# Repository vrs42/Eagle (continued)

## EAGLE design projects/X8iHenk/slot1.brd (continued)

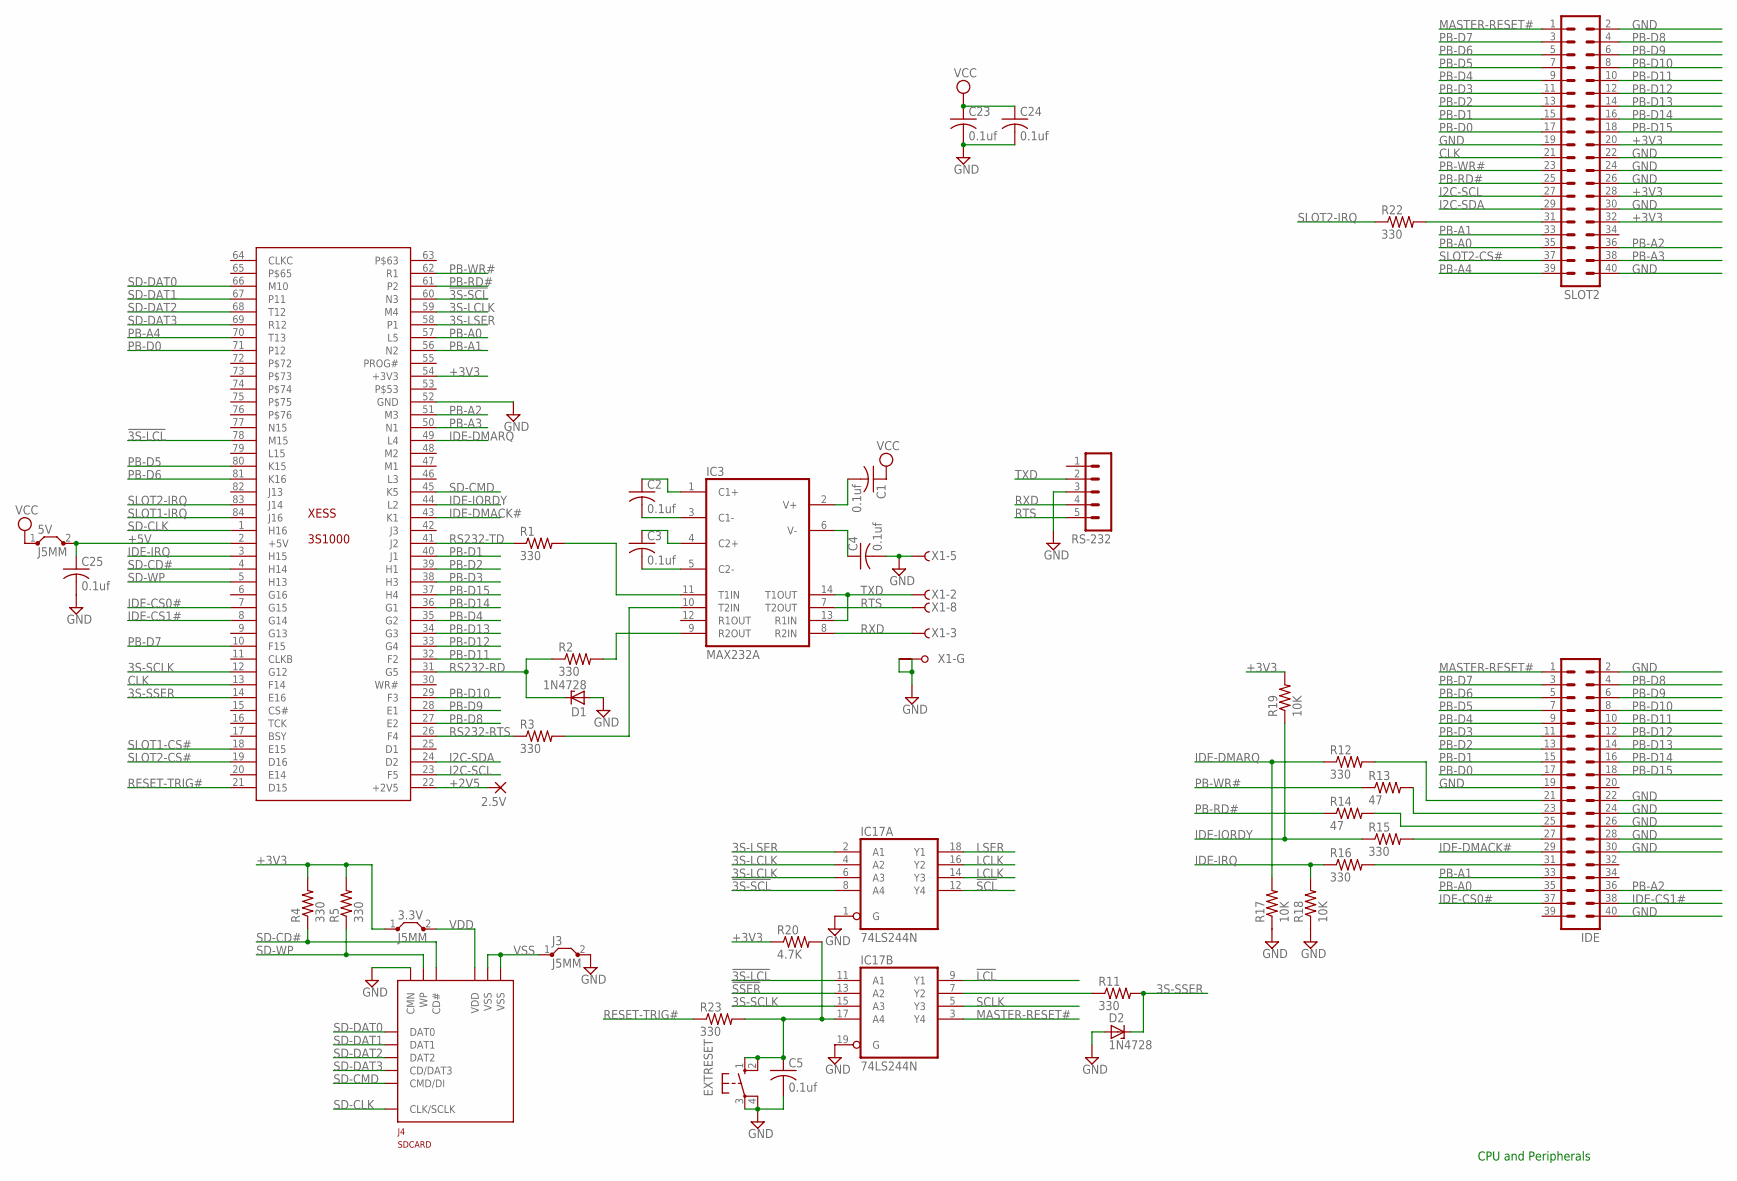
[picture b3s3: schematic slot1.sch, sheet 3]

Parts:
2.5V: 1,6/0,8
3.3V, 5V: J5MM; 05
C1, C2, C3, C4, C5, C23, C24, C25: 0.1uf; C050-025X075
D1, D2: 1N4728; DO41Z10
EXTRESET: 40-XX; B3F-40XX
IC3: MAX232A; DIL16
IC17: 74LS244N; DIL20
IDE: MA20-2
J3: J5MM; 05
J4: SDCARD; SCDA5A
R1, R2, R3, R4, R5, R11, R12, R15, R16, R22, R23: 330; 0207/10
R13, R14: 47; 0207/10
R17, R18, R19: 10K; 0207/10
R20: 4.7K; 0207/10
RS-232: MA05-1
SLOT2: MA20-2
X1: F09HPS; F09HP
XESS: 3S1000

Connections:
3S-LCLK: IC17.4 (A2), IC17.6 (A3), XESS.59 (M4)
3S-LSER: IC17.2 (A1), XESS.58 (P1)
3S-SCLK: IC17.15 (A3), XESS.12 (G12)
3S-SSER: D2.C, R11.2, XESS.14 (E16)
!3S-LCL: IC17.11 (A1), XESS.78 (M15)
!3S-SCL: IC17.8 (A4), XESS.60 (N3)
!LCL: IC17.9 (Y1)
!SCL: IC17.12 (Y4); also elsewhere on the board
!SSER: IC17.13 (A2); also elsewhere on the board
+2V5: 2.5V.1, XESS.22 (+2V5)
+3V3: 3.3V.1, R4.2, R5.2, R19.2, R20.1, SLOT2.20, SLOT2.28, SLOT2.32, XESS.54 (+3V3)
+5V: 5V.2, C25.1, XESS.2 (+5V)
CLK: SLOT2.21, XESS.13 (F14)
GND: C4.2, C5.2, C23.2, C24.2, C25.2, D1.A, D2.A, EXTRESET.3, EXTRESET.4 (P1), IC3.15 (GND), IC17.1 (G), IC17.10 (GND), IC17.19 (G), IDE.2, IDE.19, IDE.22, IDE.24, IDE.26, IDE.28, IDE.30, IDE.40, J3.2, J4.11 (CMN), J4.13 (GND), J4.14 (GND), R17.1, R18.1, RS-232.3, SLOT2.2, SLOT2.19, SLOT2.22, SLOT2.24, SLOT2.26, SLOT2.30, SLOT2.40, X1.5 (F), X1.G1, X1.G2, XESS.52 (GND); also elsewhere on the board
I2C-SCL: SLOT2.27, XESS.23 (F5)
I2C-SDA: SLOT2.29, XESS.24 (D2)
IDE-CS0#: IDE.37, XESS.7 (G15)
IDE-CS1#: IDE.38, XESS.8 (G14)
IDE-DMACK#: IDE.29, XESS.43 (K1)
IDE-DMARQ: R12.1, R17.2, XESS.49 (L4)
IDE-IORDY: R15.1, R19.1, XESS.44 (L2)
IDE-IRQ: R16.1, R18.2, XESS.3 (H15)
LCLK: IC17.14 (Y3), IC17.16 (Y2)
LSER: IC17.18 (Y1)
MASTER-RESET#: IC17.3 (Y4), IDE.1, SLOT2.1
unnamed: IC3.10 (T2IN), R3.2
unnamed: IC3.11 (T1IN), R1.2
unnamed: IC3.9 (R2OUT), R2.2
unnamed: C1.2, IC3.2 (V+)
unnamed: C2.2, IC3.3 (C1-)
unnamed: C2.1, IC3.1 (C1+)
unnamed: C4.1, IC3.6 (V-)
unnamed: C3.1, IC3.4 (C2+)
unnamed: C3.2, IC3.5 (C2-)
unnamed: IC17.7 (Y2), R11.1
unnamed: R22.2, SLOT2.31
unnamed: C5.1, EXTRESET.1 (S), EXTRESET.2 (S1), IC17.17 (A4), R20.2, R23.2
unnamed: IDE.31, R16.2
unnamed: IDE.27, R15.2
unnamed: IDE.25, R14.2
unnamed: IDE.23, R13.2
unnamed: IDE.21, R12.2
PB-A0: IDE.35, SLOT2.35, XESS.57 (L5); also elsewhere on the board
PB-A1: IDE.33, SLOT2.33, XESS.56 (N2)
PB-A2: IDE.36, SLOT2.36, XESS.51 (M3); also elsewhere on the board
PB-A3: SLOT2.38, XESS.50 (N1)
PB-A4: SLOT2.39, XESS.70 (T13)
PB-D0: IDE.17, SLOT2.17, XESS.71 (P12); also elsewhere on the board
PB-D1: IDE.15, SLOT2.15, XESS.40 (J1); also elsewhere on the board
PB-D2: IDE.13, SLOT2.13, XESS.39 (H1); also elsewhere on the board
PB-D3: IDE.11, SLOT2.11, XESS.38 (H3); also elsewhere on the board
PB-D4: IDE.9, SLOT2.9, XESS.35 (G2); also elsewhere on the board
PB-D5: IDE.7, SLOT2.7, XESS.80 (K15); also elsewhere on the board
PB-D6: IDE.5, SLOT2.5, XESS.81 (K16); also elsewhere on the board
PB-D7: IDE.3, SLOT2.3, XESS.10 (F15); also elsewhere on the board
PB-D8: IDE.4, SLOT2.4, XESS.27 (E2); also elsewhere on the board
PB-D9: IDE.6, SLOT2.6, XESS.28 (E1); also elsewhere on the board
PB-D10: IDE.8, SLOT2.8, XESS.29 (F3); also elsewhere on the board
PB-D11: IDE.10, SLOT2.10, XESS.32 (F2); also elsewhere on the board
PB-D12: IDE.12, SLOT2.12, XESS.33 (G4); also elsewhere on the board
PB-D13: IDE.14, SLOT2.14, XESS.34 (G3); also elsewhere on the board
PB-D14: IDE.16, SLOT2.16, XESS.36 (G1); also elsewhere on the board
PB-D15: IDE.18, SLOT2.18, XESS.37 (H4); also elsewhere on the board
PB-RD#: R14.1, SLOT2.25, XESS.61 (P2)
PB-WR#: R13.1, SLOT2.23, XESS.62 (R1); also elsewhere on the board
RESET-TRIG#: R23.1, XESS.21 (D15)
RS232-RD: D1.C, R2.1, XESS.31 (G5)
RS232-RTS: R3.1, XESS.26 (F4)
RS232-TD: R1.1, XESS.41 (J2)
RTS: IC3.7 (T2OUT), RS-232.5, X1.8 (F)
RXD: IC3.8 (R2IN), RS-232.4, X1.3 (F)
SCLK: IC17.5 (Y3); also elsewhere on the board
SD-CD#: J4.10 (CD#), R4.1, XESS.4 (H14)
SD-CLK: J4.5 (CLK/SCLK), XESS.1 (H16)
SD-CMD: J4.2 (CMD/DI), XESS.45 (K5)
SD-DAT0: J4.7 (DAT0), XESS.66 (M10)
SD-DAT1: J4.8 (DAT1), XESS.67 (P11)
SD-DAT2: J4.9 (DAT2), XESS.68 (T12)
SD-DAT3: J4.1 (CD/DAT3), XESS.69 (R12)
SD-WP: J4.12 (WP), R5.1, XESS.5 (H13)
SLOT1-CS#: XESS.18 (E15); also elsewhere on the board
SLOT1-IRQ: XESS.84 (J16)
SLOT2-CS#: SLOT2.37, XESS.19 (D16)
SLOT2-IRQ: R22.1, XESS.83 (J14)
TXD: IC3.13 (R1IN), IC3.14 (T1OUT), RS-232.2, X1.2 (F)
VCC: 5V.1, C1.1, C23.1, C24.1, IC3.16 (VCC), IC17.20 (VCC); also elsewhere on the board
VDD: 3.3V.2, J4.4 (VDD)
VSS: J3.1, J4.3 (VSS), J4.6 (VSS)

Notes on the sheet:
CPU and Peripherals

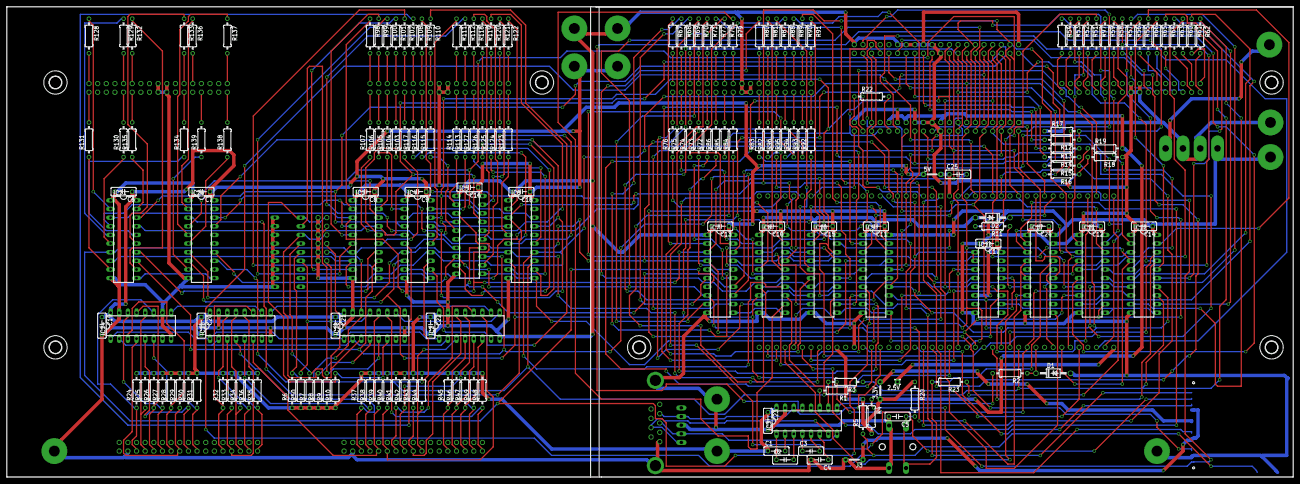
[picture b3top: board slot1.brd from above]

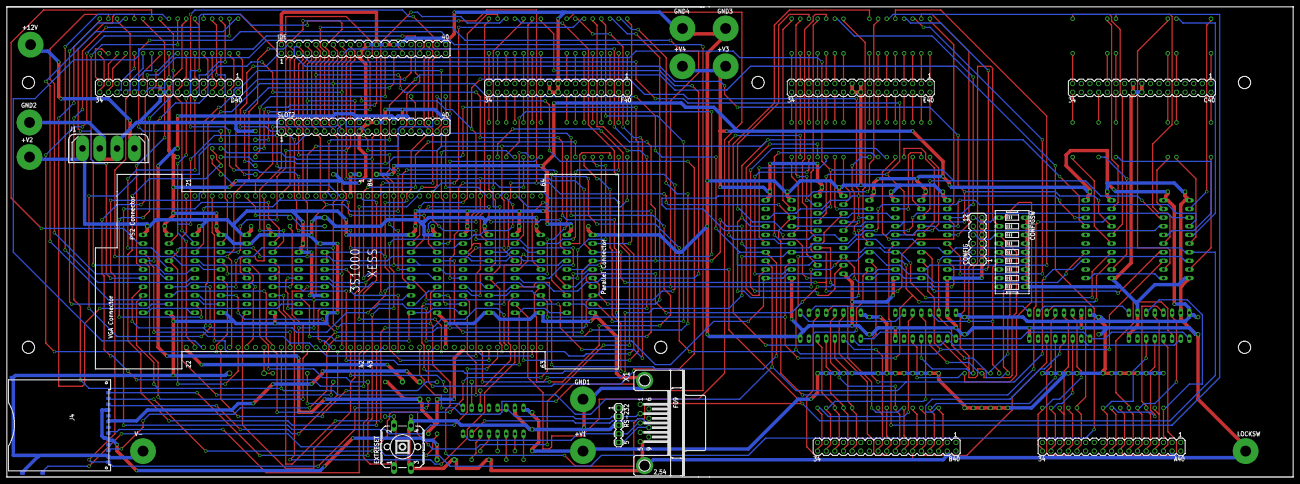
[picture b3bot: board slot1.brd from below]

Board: 2 copper layers, 377.8 x 138.1 mm, 221 parts (27 on the bottom side), 305 nets.

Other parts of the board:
U$5, U$6, U$7, U$8, U$9, U$11: 3,6

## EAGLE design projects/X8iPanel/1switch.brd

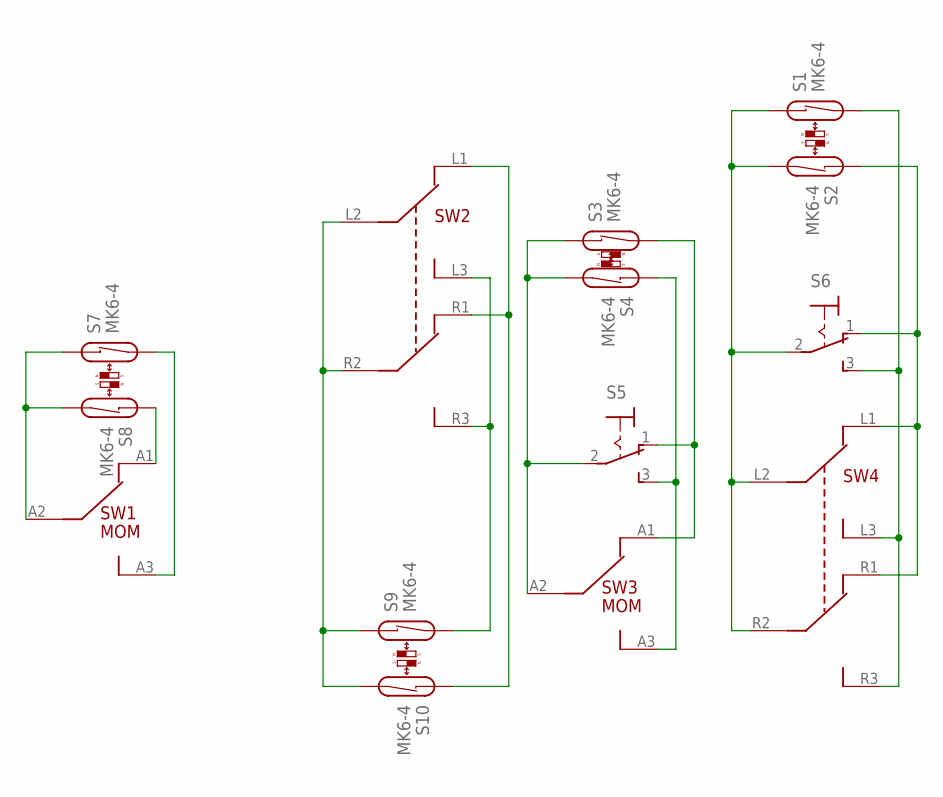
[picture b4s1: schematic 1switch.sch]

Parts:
S1, S2, S3, S4, S7, S8, S9, S10: MK6-4
S5, S6: M9040P7101V2; 7101MD9V21
SW1, SW3: SPDT8I
SW2, SW4: DPDT8I

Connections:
unnamed: S8.1, SW1.A1
unnamed: S7.2, SW1.A3
unnamed: S7.1, S8.2, SW1.A2
unnamed: S9.1, S10.2, SW2.L2 (A2), SW2.R2 (B2)
unnamed: S3.1, S4.2, S5.2, SW3.A2
unnamed: S9.2, SW2.L3 (A3), SW2.R3 (B3)
unnamed: S10.1, SW2.L1 (A1), SW2.R1 (B1)
unnamed: S4.1, S5.3 (S), SW3.A3
unnamed: S3.2, S5.1 (O), SW3.A1
unnamed: S1.1, S2.2, S6.2, SW4.L2 (A2), SW4.R2 (B2)
unnamed: S1.2, S6.3 (S), SW4.L3 (A3), SW4.R3 (B3)
unnamed: S2.1, S6.1 (O), SW4.L1 (A1), SW4.R1 (B1)

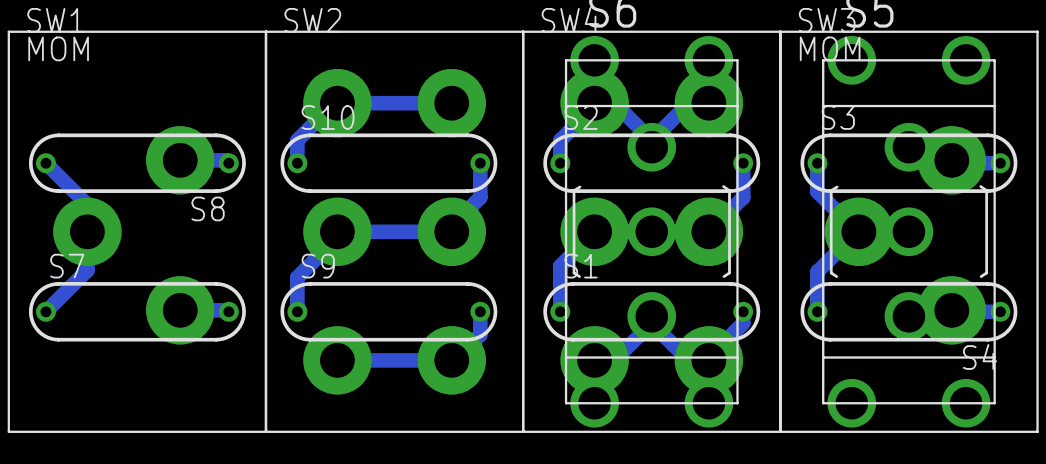
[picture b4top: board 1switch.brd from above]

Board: 2 copper layers, 14 parts (0 on the bottom side), 12 nets.

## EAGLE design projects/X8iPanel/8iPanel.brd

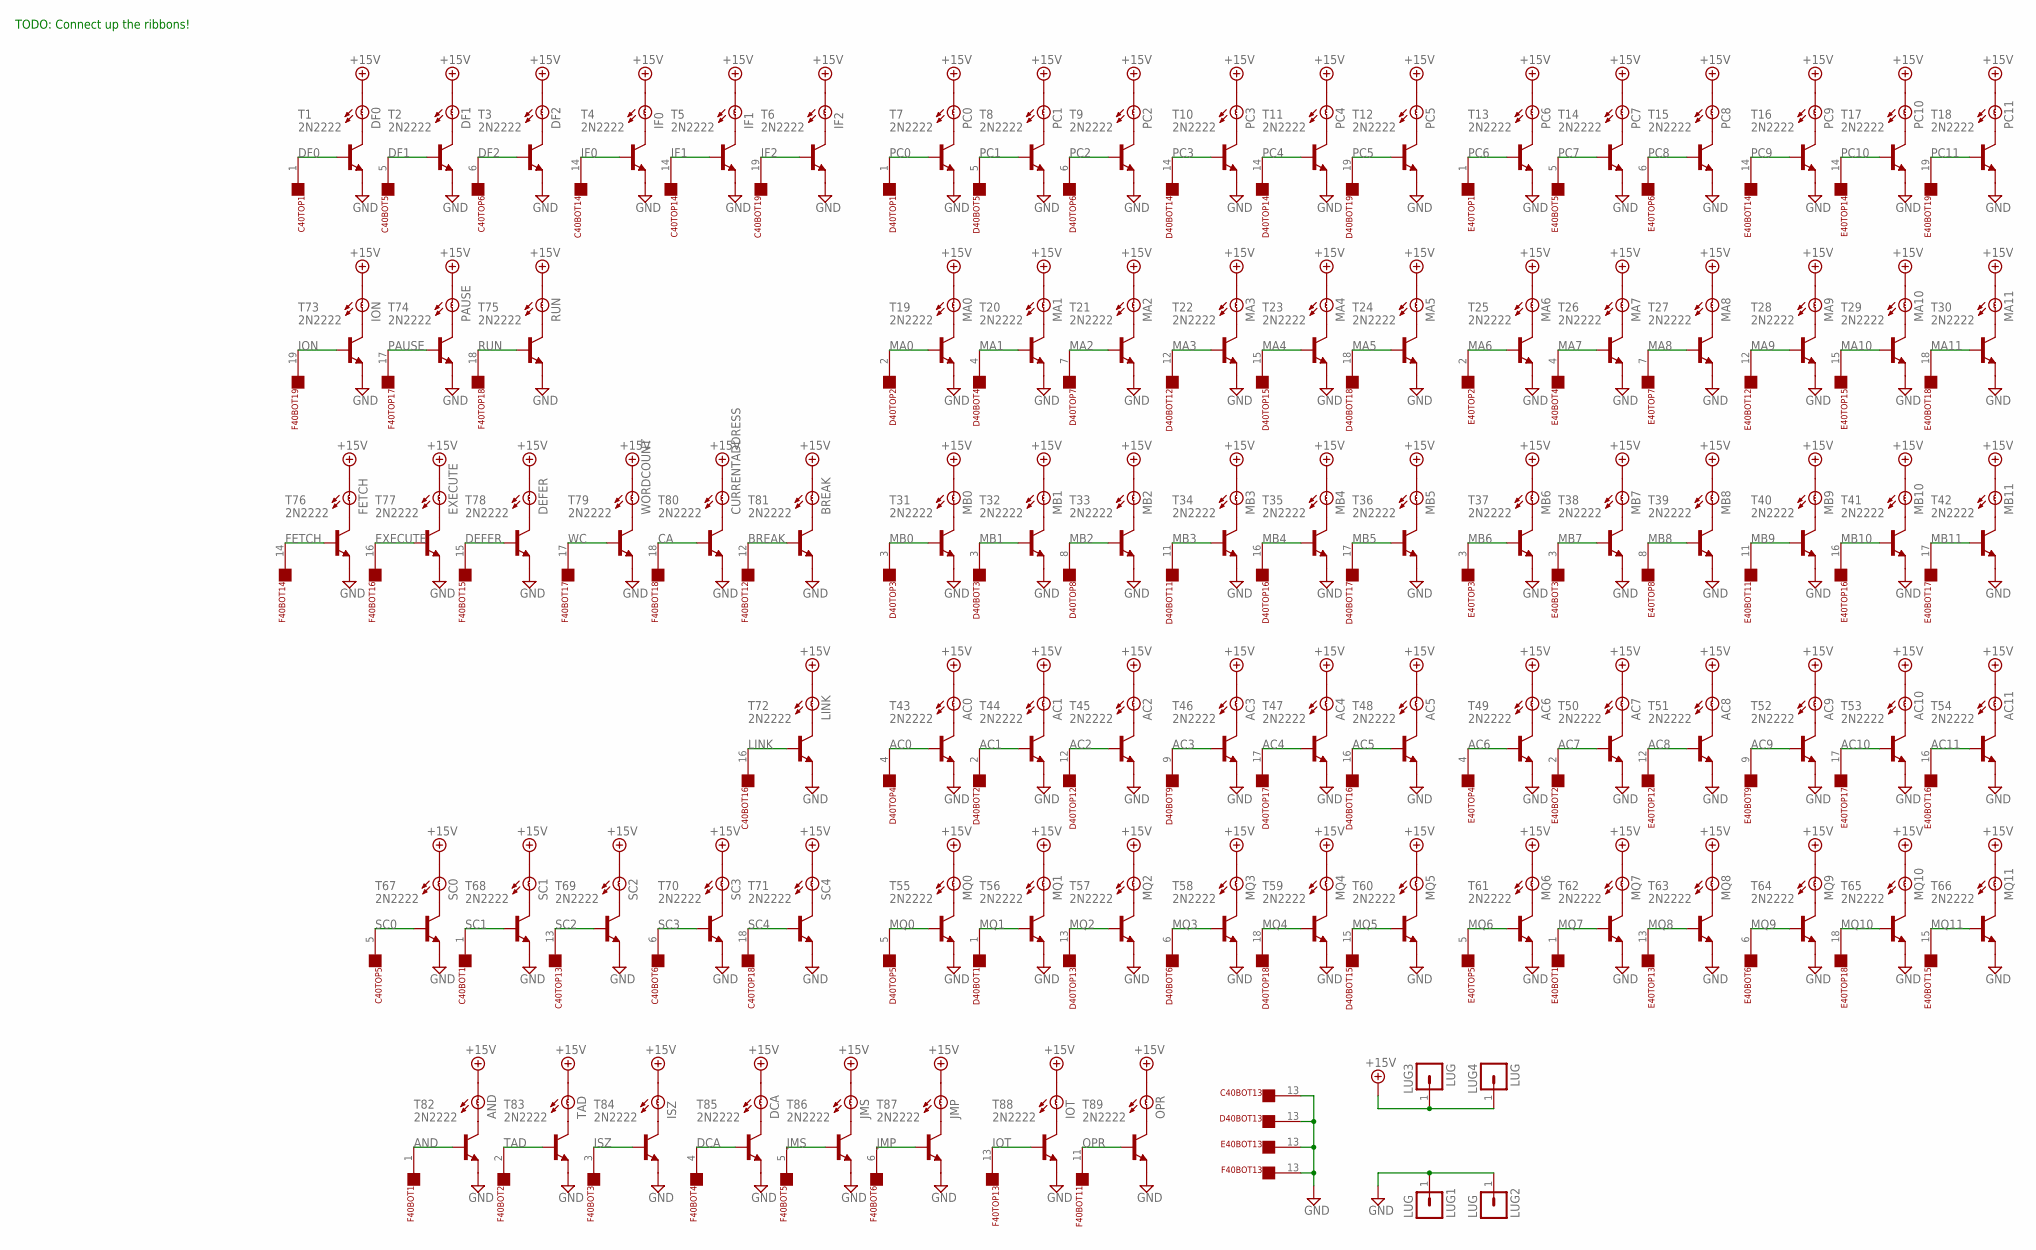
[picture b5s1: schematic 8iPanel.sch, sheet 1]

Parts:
AC0, AC1, AC2, AC3, AC4, AC5, AC6, AC7, AC8, AC9, AC10, AC11: BULB
AND: BULB
BREAK: BULB
C40BOT, C40TOP: FLEX19
CURRENTADDRESS: BULB
D40BOT, D40TOP: FLEX19
DCA: BULB
DEFER: BULB
DF0, DF1, DF2: BULB
E40BOT, E40TOP: FLEX19
EXECUTE: BULB
F40BOT, F40TOP: FLEX19
FETCH: BULB
IF0, IF1, IF2: BULB
ION: BULB
IOT: BULB
ISZ: BULB
JMP: BULB
JMS: BULB
LINK: BULB
LUG1, LUG2, LUG3, LUG4: LUG; SPADELUG
MA0, MA1, MA2, MA3, MA4, MA5, MA6, MA7, MA8, MA9, MA10, MA11: BULB
MB0, MB1, MB2, MB3, MB4, MB5, MB6, MB7, MB8, MB9, MB10, MB11: BULB
MQ0, MQ1, MQ2, MQ3, MQ4, MQ5, MQ6, MQ7, MQ8, MQ9, MQ10, MQ11: BULB
OPR: BULB
PAUSE: BULB
PC0, PC1, PC2, PC3, PC4, PC5, PC6, PC7, PC8, PC9, PC10, PC11: BULB
RUN: BULB
SC0, SC1, SC2, SC3, SC4: BULB
T1, T2, T3, T4, T5, T6, T7, T8, T9, T10, T11, T12, T13, T14, T15, T16, T17, T18, T19, T20, T21, T22, T23, T24, T25, T26, T27, T28, T29, T30, T31, T32, T33, T34, T35, T36, T37, T38, T39, T40, T41, T42, T43, T44, T45, T46, T47, T48, T49, T50, T51, T52, T53, T54, T55, T56, T57, T58, T59, T60, T61, T62, T63, T64, T65, T66, T67, T68, T69, T70, T71, T72, T73, T74, T75, T76, T77, T78, T79, T80, T81, T82, T83, T84, T85, T86, T87, T88, T89: 2N2222; TO92
TAD: BULB
WORDCOUNT: BULB

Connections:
+15V: AC0.A, AC1.A, AC2.A, AC3.A, AC4.A, AC5.A, AC6.A, AC7.A, AC8.A, AC9.A, AC10.A, AC11.A, AND.A, BREAK.A, CURRENTADDRESS.A, DCA.A, DEFER.A, DF0.A, DF1.A, DF2.A, EXECUTE.A, FETCH.A, IF0.A, IF1.A, IF2.A, ION.A, IOT.A, ISZ.A, JMP.A, JMS.A, LINK.A, LUG3.1, LUG4.1, MA0.A, MA1.A, MA2.A, MA3.A, MA4.A, MA5.A, MA6.A, MA7.A, MA8.A, MA9.A, MA10.A, MA11.A, MB0.A, MB1.A, MB2.A, MB3.A, MB4.A, MB5.A, MB6.A, MB7.A, MB8.A, MB9.A, MB10.A, MB11.A, MQ0.A, MQ1.A, MQ2.A, MQ3.A, MQ4.A, MQ5.A, MQ6.A, MQ7.A, MQ8.A, MQ9.A, MQ10.A, MQ11.A, OPR.A, PAUSE.A, PC0.A, PC1.A, PC2.A, PC3.A, PC4.A, PC5.A, PC6.A, PC7.A, PC8.A, PC9.A, PC10.A, PC11.A, RUN.A, SC0.A, SC1.A, SC2.A, SC3.A, SC4.A, TAD.A, WORDCOUNT.A
AC0: D40TOP.4, T43.2 (B); also elsewhere on the board
AC1: D40BOT.2, T44.2 (B); also elsewhere on the board
AC2: D40TOP.12, T45.2 (B); also elsewhere on the board
AC3: D40BOT.9, T46.2 (B); also elsewhere on the board
AC4: D40TOP.17, T47.2 (B); also elsewhere on the board
AC5: D40BOT.16, T48.2 (B); also elsewhere on the board
AC6: E40TOP.4, T49.2 (B); also elsewhere on the board
AC7: E40BOT.2, T50.2 (B); also elsewhere on the board
AC8: E40TOP.12, T51.2 (B); also elsewhere on the board
AC9: E40BOT.9, T52.2 (B); also elsewhere on the board
AC10: E40TOP.17, T53.2 (B); also elsewhere on the board
AC11: E40BOT.16, T54.2 (B); also elsewhere on the board
AND: F40BOT.1, T82.2 (B); also elsewhere on the board
BREAK: F40BOT.12, T81.2 (B); also elsewhere on the board
CA: F40BOT.18, T80.2 (B); also elsewhere on the board
DCA: F40BOT.4, T85.2 (B); also elsewhere on the board
DEFER: F40BOT.15, T78.2 (B); also elsewhere on the board
DF0: C40TOP.1, T1.2 (B); also elsewhere on the board
DF1: C40BOT.5, T2.2 (B); also elsewhere on the board
DF2: C40TOP.6, T3.2 (B); also elsewhere on the board
EXECUTE: F40BOT.16, T77.2 (B); also elsewhere on the board
FETCH: F40BOT.14, T76.2 (B); also elsewhere on the board
GND: C40BOT.13, D40BOT.13, E40BOT.13, F40BOT.13, LUG1.1, LUG2.1, T1.1 (E), T2.1 (E), T3.1 (E), T4.1 (E), T5.1 (E), T6.1 (E), T7.1 (E), T8.1 (E), T9.1 (E), T10.1 (E), T11.1 (E), T12.1 (E), T13.1 (E), T14.1 (E), T15.1 (E), T16.1 (E), T17.1 (E), T18.1 (E), T19.1 (E), T20.1 (E), T21.1 (E), T22.1 (E), T23.1 (E), T24.1 (E), T25.1 (E), T26.1 (E), T27.1 (E), T28.1 (E), T29.1 (E), T30.1 (E), T31.1 (E), T32.1 (E), T33.1 (E), T34.1 (E), T35.1 (E), T36.1 (E), T37.1 (E), T38.1 (E), T39.1 (E), T40.1 (E), T41.1 (E), T42.1 (E), T43.1 (E), T44.1 (E), T45.1 (E), T46.1 (E), T47.1 (E), T48.1 (E), T49.1 (E), T50.1 (E), T51.1 (E), T52.1 (E), T53.1 (E), T54.1 (E), T55.1 (E), T56.1 (E), T57.1 (E), T58.1 (E), T59.1 (E), T60.1 (E), T61.1 (E), T62.1 (E), T63.1 (E), T64.1 (E), T65.1 (E), T66.1 (E), T67.1 (E), T68.1 (E), T69.1 (E), T70.1 (E), T71.1 (E), T72.1 (E), T73.1 (E), T74.1 (E), T75.1 (E), T76.1 (E), T77.1 (E), T78.1 (E), T79.1 (E), T80.1 (E), T81.1 (E), T82.1 (E), T83.1 (E), T84.1 (E), T85.1 (E), T86.1 (E), T87.1 (E), T88.1 (E), T89.1 (E); also elsewhere on the board
IF0: C40BOT.14, T4.2 (B); also elsewhere on the board
IF1: C40TOP.14, T5.2 (B); also elsewhere on the board
IF2: C40BOT.19, T6.2 (B); also elsewhere on the board
ION: F40BOT.19, T73.2 (B); also elsewhere on the board
IOT: F40TOP.13, T88.2 (B); also elsewhere on the board
ISZ: F40BOT.3, T84.2 (B); also elsewhere on the board
JMP: F40BOT.6, T87.2 (B); also elsewhere on the board
JMS: F40BOT.5, T86.2 (B); also elsewhere on the board
LINK: C40BOT.16, T72.2 (B); also elsewhere on the board
MA0: D40TOP.2, T19.2 (B); also elsewhere on the board
MA1: D40BOT.4, T20.2 (B); also elsewhere on the board
MA2: D40TOP.7, T21.2 (B); also elsewhere on the board
MA3: D40BOT.12, T22.2 (B); also elsewhere on the board
MA4: D40TOP.15, T23.2 (B); also elsewhere on the board
MA5: D40BOT.18, T24.2 (B); also elsewhere on the board
MA6: E40TOP.2, T25.2 (B); also elsewhere on the board
MA7: E40BOT.4, T26.2 (B); also elsewhere on the board
MA8: E40TOP.7, T27.2 (B); also elsewhere on the board
MA9: E40BOT.12, T28.2 (B); also elsewhere on the board
MA10: E40TOP.15, T29.2 (B); also elsewhere on the board
MA11: E40BOT.18, T30.2 (B); also elsewhere on the board
MB0: D40TOP.3, T31.2 (B); also elsewhere on the board
MB1: D40BOT.3, T32.2 (B); also elsewhere on the board
MB2: D40TOP.8, T33.2 (B); also elsewhere on the board
MB3: D40BOT.11, T34.2 (B); also elsewhere on the board
MB4: D40TOP.16, T35.2 (B); also elsewhere on the board
MB5: D40BOT.17, T36.2 (B); also elsewhere on the board
MB6: E40TOP.3, T37.2 (B); also elsewhere on the board
MB7: E40BOT.3, T38.2 (B); also elsewhere on the board
MB8: E40TOP.8, T39.2 (B); also elsewhere on the board
MB9: E40BOT.11, T40.2 (B); also elsewhere on the board
MB10: E40TOP.16, T41.2 (B); also elsewhere on the board
MB11: E40BOT.17, T42.2 (B); also elsewhere on the board
MQ0: D40TOP.5, T55.2 (B); also elsewhere on the board
MQ1: D40BOT.1, T56.2 (B); also elsewhere on the board
MQ2: D40TOP.13, T57.2 (B); also elsewhere on the board
MQ3: D40BOT.6, T58.2 (B); also elsewhere on the board
MQ4: D40TOP.18, T59.2 (B); also elsewhere on the board
MQ5: D40BOT.15, T60.2 (B); also elsewhere on the board
MQ6: E40TOP.5, T61.2 (B); also elsewhere on the board
MQ7: E40BOT.1, T62.2 (B); also elsewhere on the board
MQ8: E40TOP.13, T63.2 (B); also elsewhere on the board
MQ9: E40BOT.6, T64.2 (B); also elsewhere on the board
MQ10: E40TOP.18, T65.2 (B); also elsewhere on the board
MQ11: E40BOT.15, T66.2 (B); also elsewhere on the board
unnamed: DF0.B, T1.3 (C)
unnamed: DF1.B, T2.3 (C)
unnamed: DF2.B, T3.3 (C)
unnamed: IF0.B, T4.3 (C)
unnamed: IF1.B, T5.3 (C)
unnamed: IF2.B, T6.3 (C)
unnamed: PC0.B, T7.3 (C)
unnamed: PC1.B, T8.3 (C)
unnamed: PC2.B, T9.3 (C)
unnamed: PC3.B, T10.3 (C)
unnamed: PC4.B, T11.3 (C)
unnamed: PC5.B, T12.3 (C)
unnamed: PC6.B, T13.3 (C)
unnamed: PC7.B, T14.3 (C)
unnamed: PC8.B, T15.3 (C)
unnamed: PC9.B, T16.3 (C)
unnamed: PC10.B, T17.3 (C)
unnamed: PC11.B, T18.3 (C)
unnamed: MA0.B, T19.3 (C)
unnamed: MA1.B, T20.3 (C)
unnamed: MA2.B, T21.3 (C)
unnamed: MA3.B, T22.3 (C)
unnamed: MA4.B, T23.3 (C)
unnamed: MA5.B, T24.3 (C)
unnamed: MA6.B, T25.3 (C)
unnamed: MA7.B, T26.3 (C)
unnamed: MA8.B, T27.3 (C)
unnamed: MA9.B, T28.3 (C)
unnamed: MA10.B, T29.3 (C)
unnamed: MA11.B, T30.3 (C)
unnamed: MB0.B, T31.3 (C)
unnamed: MB1.B, T32.3 (C)
unnamed: MB2.B, T33.3 (C)
unnamed: MB3.B, T34.3 (C)
unnamed: MB4.B, T35.3 (C)
unnamed: MB5.B, T36.3 (C)
unnamed: MB6.B, T37.3 (C)
unnamed: MB7.B, T38.3 (C)
unnamed: MB8.B, T39.3 (C)
unnamed: MB9.B, T40.3 (C)
unnamed: MB10.B, T41.3 (C)
unnamed: MB11.B, T42.3 (C)
unnamed: AC0.B, T43.3 (C)
unnamed: AC1.B, T44.3 (C)
unnamed: AC2.B, T45.3 (C)
unnamed: AC3.B, T46.3 (C)
unnamed: AC4.B, T47.3 (C)
unnamed: AC5.B, T48.3 (C)
unnamed: AC6.B, T49.3 (C)
unnamed: AC7.B, T50.3 (C)
unnamed: AC8.B, T51.3 (C)
unnamed: AC9.B, T52.3 (C)
unnamed: AC10.B, T53.3 (C)
unnamed: AC11.B, T54.3 (C)
unnamed: MQ0.B, T55.3 (C)
unnamed: MQ1.B, T56.3 (C)
unnamed: MQ2.B, T57.3 (C)
unnamed: MQ3.B, T58.3 (C)
unnamed: MQ4.B, T59.3 (C)
unnamed: MQ5.B, T60.3 (C)
unnamed: MQ6.B, T61.3 (C)
unnamed: MQ7.B, T62.3 (C)
unnamed: MQ8.B, T63.3 (C)
unnamed: MQ9.B, T64.3 (C)
unnamed: MQ10.B, T65.3 (C)
unnamed: MQ11.B, T66.3 (C)
unnamed: SC0.B, T67.3 (C)
unnamed: SC1.B, T68.3 (C)
unnamed: SC2.B, T69.3 (C)
unnamed: SC3.B, T70.3 (C)
unnamed: SC4.B, T71.3 (C)
unnamed: LINK.B, T72.3 (C)
unnamed: ION.B, T73.3 (C)
unnamed: PAUSE.B, T74.3 (C)
unnamed: RUN.B, T75.3 (C)
unnamed: FETCH.B, T76.3 (C)
unnamed: EXECUTE.B, T77.3 (C)
unnamed: DEFER.B, T78.3 (C)
unnamed: T79.3 (C), WORDCOUNT.B
unnamed: CURRENTADDRESS.B, T80.3 (C)
unnamed: BREAK.B, T81.3 (C)
unnamed: AND.B, T82.3 (C)
unnamed: T83.3 (C), TAD.B
unnamed: ISZ.B, T84.3 (C)
unnamed: DCA.B, T85.3 (C)
unnamed: JMS.B, T86.3 (C)
unnamed: JMP.B, T87.3 (C)
unnamed: IOT.B, T88.3 (C)
unnamed: OPR.B, T89.3 (C)
OPR: F40BOT.11, T89.2 (B); also elsewhere on the board
PAUSE: F40TOP.17, T74.2 (B); also elsewhere on the board
PC0: D40TOP.1, T7.2 (B); also elsewhere on the board
PC1: D40BOT.5, T8.2 (B); also elsewhere on the board
PC2: D40TOP.6, T9.2 (B); also elsewhere on the board
PC3: D40BOT.14, T10.2 (B); also elsewhere on the board
PC4: D40TOP.14, T11.2 (B); also elsewhere on the board
PC5: D40BOT.19, T12.2 (B); also elsewhere on the board
PC6: E40TOP.1, T13.2 (B); also elsewhere on the board
PC7: E40BOT.5, T14.2 (B); also elsewhere on the board
PC8: E40TOP.6, T15.2 (B); also elsewhere on the board
PC9: E40BOT.14, T16.2 (B); also elsewhere on the board
PC10: E40TOP.14, T17.2 (B); also elsewhere on the board
PC11: E40BOT.19, T18.2 (B); also elsewhere on the board
RUN: F40TOP.18, T75.2 (B); also elsewhere on the board
SC0: C40TOP.5, T67.2 (B); also elsewhere on the board
SC1: C40BOT.1, T68.2 (B); also elsewhere on the board
SC2: C40TOP.13, T69.2 (B); also elsewhere on the board
SC3: C40BOT.6, T70.2 (B); also elsewhere on the board
SC4: C40TOP.18, T71.2 (B); also elsewhere on the board
TAD: F40BOT.2, T83.2 (B); also elsewhere on the board
WC: F40BOT.17, T79.2 (B); also elsewhere on the board

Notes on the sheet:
TODO: Connect up the ribbons!

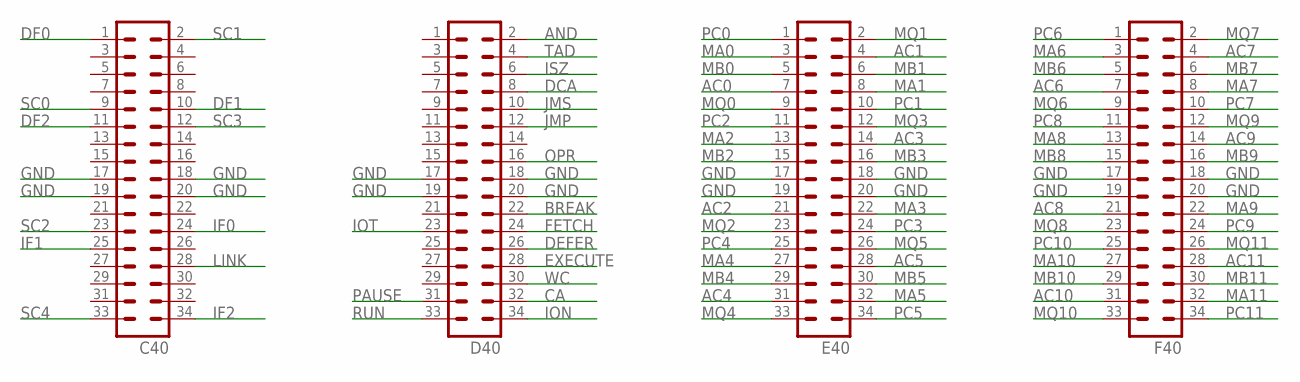
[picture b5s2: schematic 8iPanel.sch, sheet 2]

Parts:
C40: MA17-2
D40: MA17-2
E40: MA17-2
F40: MA17-2

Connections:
AC0: E40.7; also elsewhere on the board
AC1: E40.4; also elsewhere on the board
AC2: E40.21; also elsewhere on the board
AC3: E40.14; also elsewhere on the board
AC4: E40.31; also elsewhere on the board
AC5: E40.28; also elsewhere on the board
AC6: F40.7; also elsewhere on the board
AC7: F40.4; also elsewhere on the board
AC8: F40.21; also elsewhere on the board
AC9: F40.14; also elsewhere on the board
AC10: F40.31; also elsewhere on the board
AC11: F40.28; also elsewhere on the board
AND: D40.2; also elsewhere on the board
BREAK: D40.22; also elsewhere on the board
CA: D40.32; also elsewhere on the board
DCA: D40.8; also elsewhere on the board
DEFER: D40.26; also elsewhere on the board
DF0: C40.1; also elsewhere on the board
DF1: C40.10; also elsewhere on the board
DF2: C40.11; also elsewhere on the board
EXECUTE: D40.28; also elsewhere on the board
FETCH: D40.24; also elsewhere on the board
GND: C40.17, C40.18, C40.19, C40.20, D40.17, D40.18, D40.19, D40.20, E40.17, E40.18, E40.19, E40.20, F40.17, F40.18, F40.19, F40.20; also elsewhere on the board
IF0: C40.24; also elsewhere on the board
IF1: C40.25; also elsewhere on the board
IF2: C40.34; also elsewhere on the board
ION: D40.34; also elsewhere on the board
IOT: D40.23; also elsewhere on the board
ISZ: D40.6; also elsewhere on the board
JMP: D40.12; also elsewhere on the board
JMS: D40.10; also elsewhere on the board
LINK: C40.28; also elsewhere on the board
MA0: E40.3; also elsewhere on the board
MA1: E40.8; also elsewhere on the board
MA2: E40.13; also elsewhere on the board
MA3: E40.22; also elsewhere on the board
MA4: E40.27; also elsewhere on the board
MA5: E40.32; also elsewhere on the board
MA6: F40.3; also elsewhere on the board
MA7: F40.8; also elsewhere on the board
MA8: F40.13; also elsewhere on the board
MA9: F40.22; also elsewhere on the board
MA10: F40.27; also elsewhere on the board
MA11: F40.32; also elsewhere on the board
MB0: E40.5; also elsewhere on the board
MB1: E40.6; also elsewhere on the board
MB2: E40.15; also elsewhere on the board
MB3: E40.16; also elsewhere on the board
MB4: E40.29; also elsewhere on the board
MB5: E40.30; also elsewhere on the board
MB6: F40.5; also elsewhere on the board
MB7: F40.6; also elsewhere on the board
MB8: F40.15; also elsewhere on the board
MB9: F40.16; also elsewhere on the board
MB10: F40.29; also elsewhere on the board
MB11: F40.30; also elsewhere on the board
MQ0: E40.9; also elsewhere on the board
MQ1: E40.2; also elsewhere on the board
MQ2: E40.23; also elsewhere on the board
MQ3: E40.12; also elsewhere on the board
MQ4: E40.33; also elsewhere on the board
MQ5: E40.26; also elsewhere on the board
MQ6: F40.9; also elsewhere on the board
MQ7: F40.2; also elsewhere on the board
MQ8: F40.23; also elsewhere on the board
MQ9: F40.12; also elsewhere on the board
MQ10: F40.33; also elsewhere on the board
MQ11: F40.26; also elsewhere on the board
OPR: D40.16; also elsewhere on the board
PAUSE: D40.31; also elsewhere on the board
PC0: E40.1; also elsewhere on the board
PC1: E40.10; also elsewhere on the board
PC2: E40.11; also elsewhere on the board
PC3: E40.24; also elsewhere on the board
PC4: E40.25; also elsewhere on the board
PC5: E40.34; also elsewhere on the board
PC6: F40.1; also elsewhere on the board
PC7: F40.10; also elsewhere on the board
PC8: F40.11; also elsewhere on the board
PC9: F40.24; also elsewhere on the board
PC10: F40.25; also elsewhere on the board
PC11: F40.34; also elsewhere on the board
RUN: D40.33; also elsewhere on the board
SC0: C40.9; also elsewhere on the board
SC1: C40.2; also elsewhere on the board
SC2: C40.23; also elsewhere on the board
SC3: C40.12; also elsewhere on the board
SC4: C40.33; also elsewhere on the board
TAD: D40.4; also elsewhere on the board
WC: D40.30; also elsewhere on the board

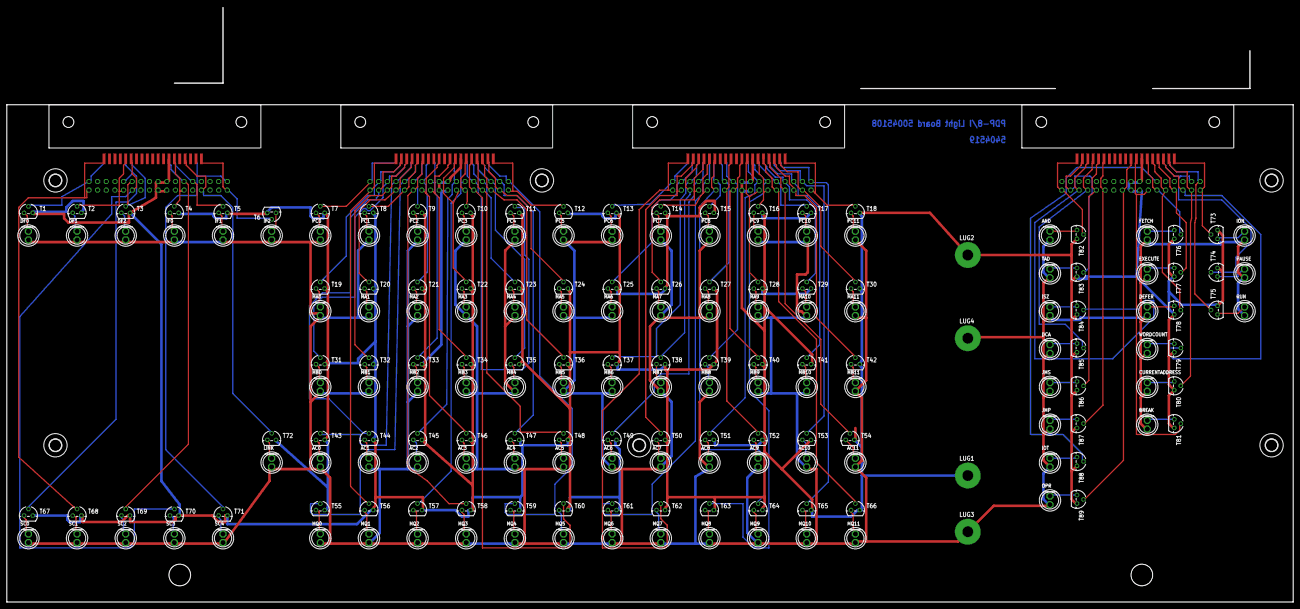
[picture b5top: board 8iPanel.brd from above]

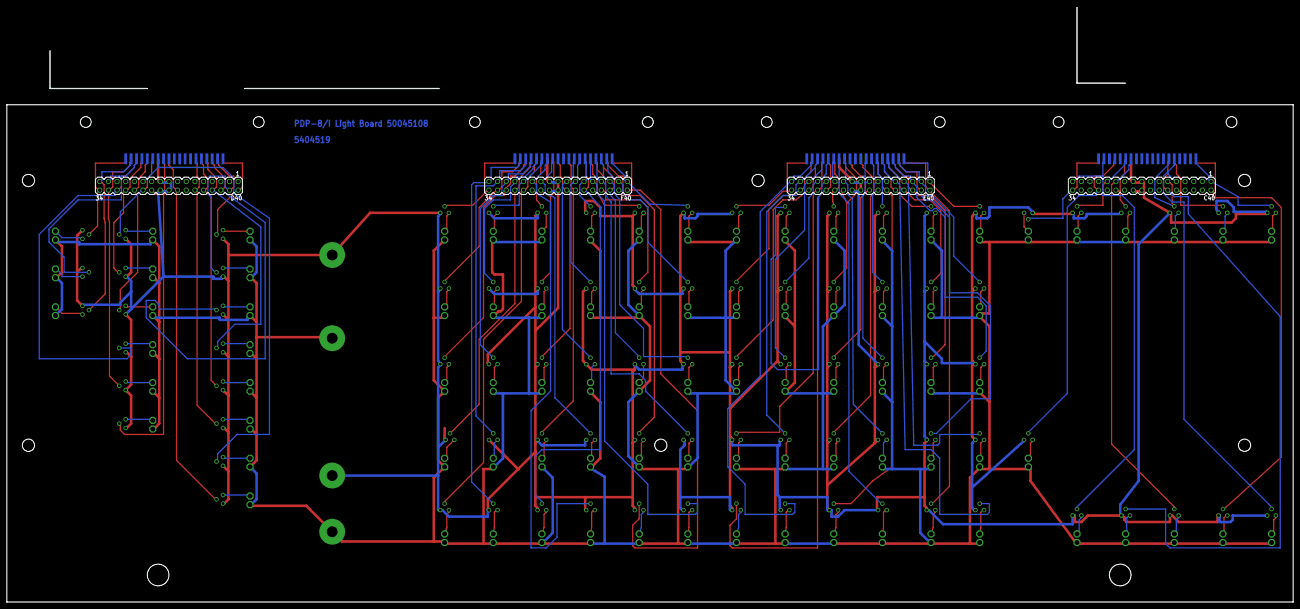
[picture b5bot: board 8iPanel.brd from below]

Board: 2 copper layers, 377.8 x 146.1 mm, 204 parts (8 on the bottom side), 180 nets.

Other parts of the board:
U$1, U$2, U$3, U$4: STRAIN-RELIEF
U$5, U$6, U$7, U$8, U$9, U$11: 3,6
